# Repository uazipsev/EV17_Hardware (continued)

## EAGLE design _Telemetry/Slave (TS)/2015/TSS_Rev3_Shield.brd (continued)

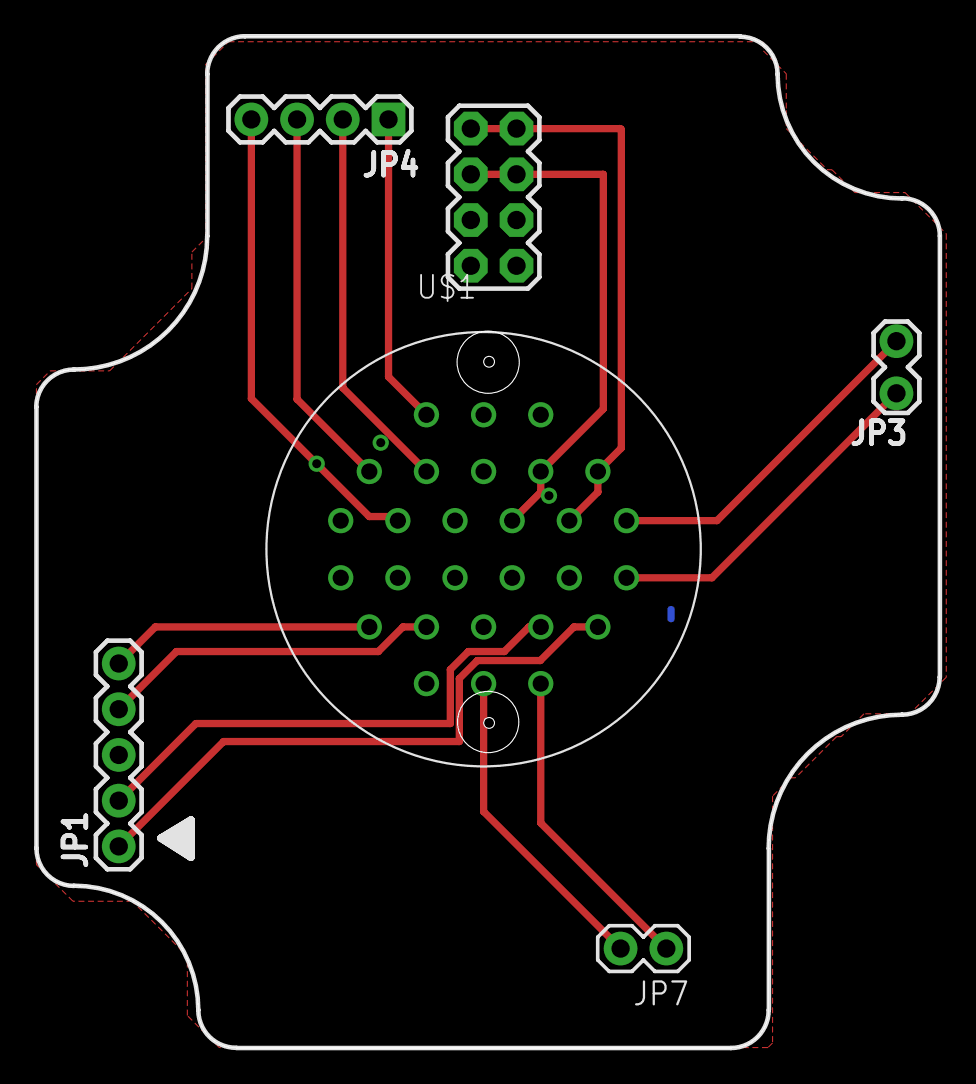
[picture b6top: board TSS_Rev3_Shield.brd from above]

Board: 2 copper layers, 50.2 x 56.2 mm, 6 parts (0 on the bottom side), 14 nets.

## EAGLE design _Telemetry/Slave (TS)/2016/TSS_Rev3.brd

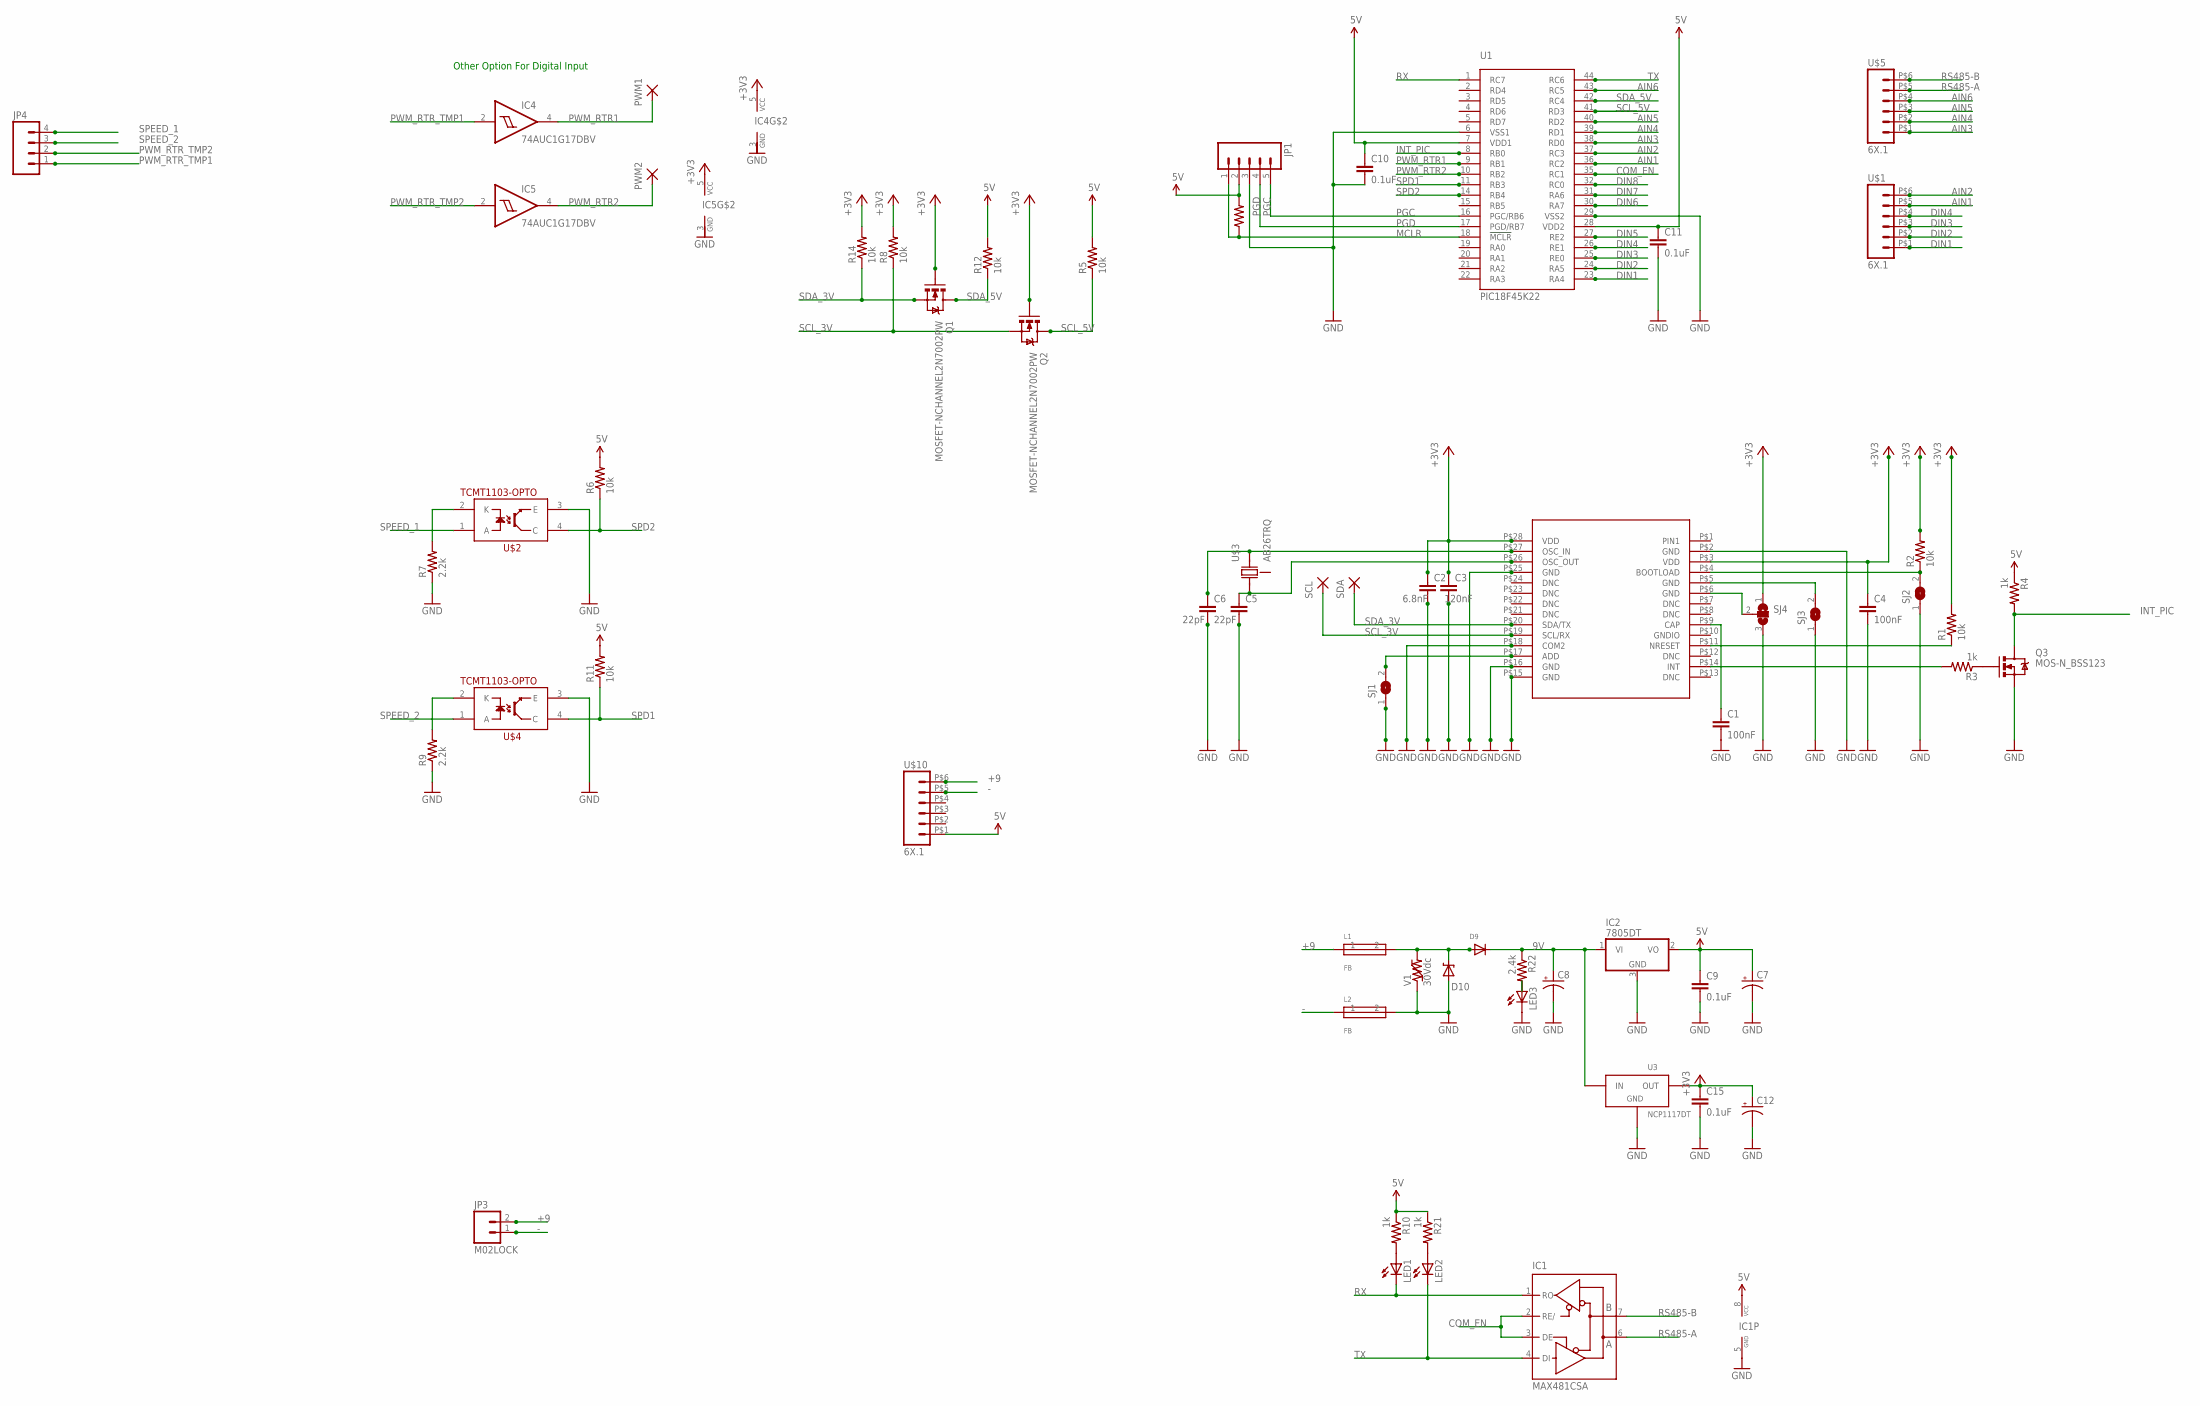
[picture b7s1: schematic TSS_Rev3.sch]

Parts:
C1, C4: 100nF; 0805
C2: 6.8nF; 0805
C3: 120nF; 0805
C5, C6: 22pF; 0805
C7, C12: CPOL-USCT3528; CT3528
C8: CAP_POL7343; EIA7343
C9, C10, C11, C15: 0.1uF; 0805
D9: DIODESOD-123; SOD-123
D10: MM5Z30; SOD-523F
IC1: MAX481CSA; SO08
IC2: 7805DT; TO252
IC4, IC5: 74AUC1G17DBV; SOT23-5
JP1: M05LOCK; 1X05_LOCK
JP3: M02LOCK; 1X02_LOCK
JP4: M04LOCK; 1X04_LOCK
L1, L2: FB; 0603
LED1, LED2, LED3: LEDCHIP-LED0805; CHIP-LED0805
PWM1, PWM2: TPSMD; 0603
Q1, Q2: MOSFET-NCHANNEL2N7002PW; SOT323
Q3: MOS-N_BSS123; SOT23
R1, R2, R5, R6, R8, R11, R12, R13, R14: 10k; 0805
R3, R4, R10, R21: 1k; 0805
R7, R9: 2.2k; 0805
R22: 2.4k; 0805
SCL: TPSMD; 0603
SDA: TPSMD; 0603
SJ1, SJ2, SJ3: SJ
SJ4: SJ2W; SJ_2
U1: PIC18F45K22; TQFP-44
U2: BOSCH_IMUSURFACEMOUNT; LGA_28
U3: NCP1117DT; DPAK
U$1, U$5, U$10: 6X.1; 1X06
U$2, U$4: TCMT1103-OPTO; SSOP-4
U$3: AB26TRQ; 3PAD_CAN
V1: 30Vdc; 0603

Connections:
5V: C7.+, C9.1, C10.1, C11.1, IC1.8 (VCC), IC2.2 (VO), JP1.2, R4.1, R5.2, R6.2, R10.1, R11.2, R12.2, R13.2, R21.1, U1.7 (VDD1), U1.28 (VDD2), U$10.P$1 (1)
9V: C8.A (+), D9.C, IC2.1 (VI), R22.1, U3.3 (IN)
+3V3: C2.1, C3.1, C4.1, C12.+, C15.1, IC4.5 (VCC), IC5.5 (VCC), Q1.1 (G), Q2.1 (G), R1.2, R2.2, R8.2, R14.2, SJ4.1, U2.P$3 (VDD), U2.P$28 (VDD), U3.2 (OUT)
+9: JP3.2, L1.1, U$10.P$6 (6)
-: JP3.1, L2.1, U$10.P$5 (5)
AIN1: U1.36 (RC2), U$1.P$5 (5)
AIN2: U1.37 (RC3), U$1.P$6 (6)
AIN3: U1.38 (RD0), U$5.P$1 (1)
AIN4: U1.39 (RD1), U$5.P$2 (2)
AIN5: U1.40 (RD2), U$5.P$3 (3)
AIN6: U1.43 (RC5), U$5.P$4 (4)
COM_EN: IC1.2 (RE/), IC1.3 (DE), U1.35 (RC1)
DIN1: U1.23 (RA4), U$1.P$1 (1)
DIN2: U1.24 (RA5), U$1.P$2 (2)
DIN3: U1.25 (RE0), U$1.P$3 (3)
DIN4: U1.26 (RE1), U$1.P$4 (4)
DIN5: U1.27 (RE2)
DIN6: U1.30 (RA7)
DIN7: U1.31 (RA6)
DIN8: U1.32 (RC0)
GHT: D9.A, D10.C, L1.2, V1.2
GND: C1.2, C2.2, C3.2, C4.2, C5.2, C6.2, C7.-, C8.C (-), C9.2, C10.2, C11.2, C12.-, C15.2, D10.A, IC1.5 (GND), IC2.3 (GND), IC4.3 (GND), IC5.3 (GND), JP1.3, L2.2, LED3.C, Q3.2 (S), R7.1, R9.1, SJ1.1, SJ2.1, SJ3.1, SJ4.3, U1.6 (VSS1), U1.29 (VSS2), U2.P$2 (GND), U2.P$15 (GND), U2.P$16 (GND), U2.P$18 (COM2), U2.P$25 (GND), U3.1 (GND), U$2.3 (E), U$4.3 (E), V1.1
INT_PIC: Q3.3 (D), R4.2, U1.8 (RB0)
MCLR: JP1.1, R13.1, U1.18 (!MCLR)
unnamed: SJ3.2, U2.P$5 (GND)
unnamed: R2.1, SJ2.2, U2.P$4 (BOOTLOAD)
unnamed: SJ4.2, U2.P$6 (GND)
unnamed: LED3.A, R22.2
unnamed: LED1.A, R10.2
unnamed: LED2.A, R21.2
unnamed: C6.1, U2.P$27 (OSC_IN), U$3.2 (OUT)
unnamed: C5.1, U2.P$26 (OSC_OUT), U$3.1 (IN)
unnamed: R7.2, U$2.2 (K)
unnamed: SJ1.2, U2.P$17 (ADD)
unnamed: R9.2, U$4.2 (K)
unnamed: R3.2, U2.P$14 (INT)
unnamed: C1.1, U2.P$9 (CAP)
unnamed: R1.1, U2.P$11 (NRESET)
unnamed: Q3.1 (G), R3.1
PGC: JP1.5, U1.16 (PGC/RB6)
PGD: JP1.4, U1.17 (PGD/RB7)
PWM_RTR1: IC4.4 (O), PWM1.1, PWM1.2, U1.9 (RB1)
PWM_RTR2: IC5.4 (O), PWM2.1, PWM2.2, U1.10 (RB2)
PWM_RTR_TMP1: IC4.2 (I), JP4.1
PWM_RTR_TMP2: IC5.2 (I), JP4.2
RS485-A: IC1.6 (A), U$5.P$5 (5)
RS485-B: IC1.7 (B), U$5.P$6 (6)
RX: IC1.1 (RO), LED1.C, U1.1 (RC7)
SCL_3V: Q2.2 (S), R8.1, SCL.1, SCL.2, U2.P$19 (SCL/RX)
SCL_5V: Q2.3 (D), R5.1, U1.41 (RD3)
SDA_3V: Q1.2 (S), R14.1, SDA.1, SDA.2, U2.P$20 (SDA/TX)
SDA_5V: Q1.3 (D), R12.1, U1.42 (RC4)
SPD1: R11.1, U1.11 (RB3), U$4.4 (C)
SPD2: R6.1, U1.14 (RB4), U$2.4 (C)
SPEED_1: JP4.4, U$2.1 (A)
SPEED_2: JP4.3, U$4.1 (A)
TX: IC1.4 (DI), LED2.C, U1.44 (RC6)

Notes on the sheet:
Other Option For Digital Input

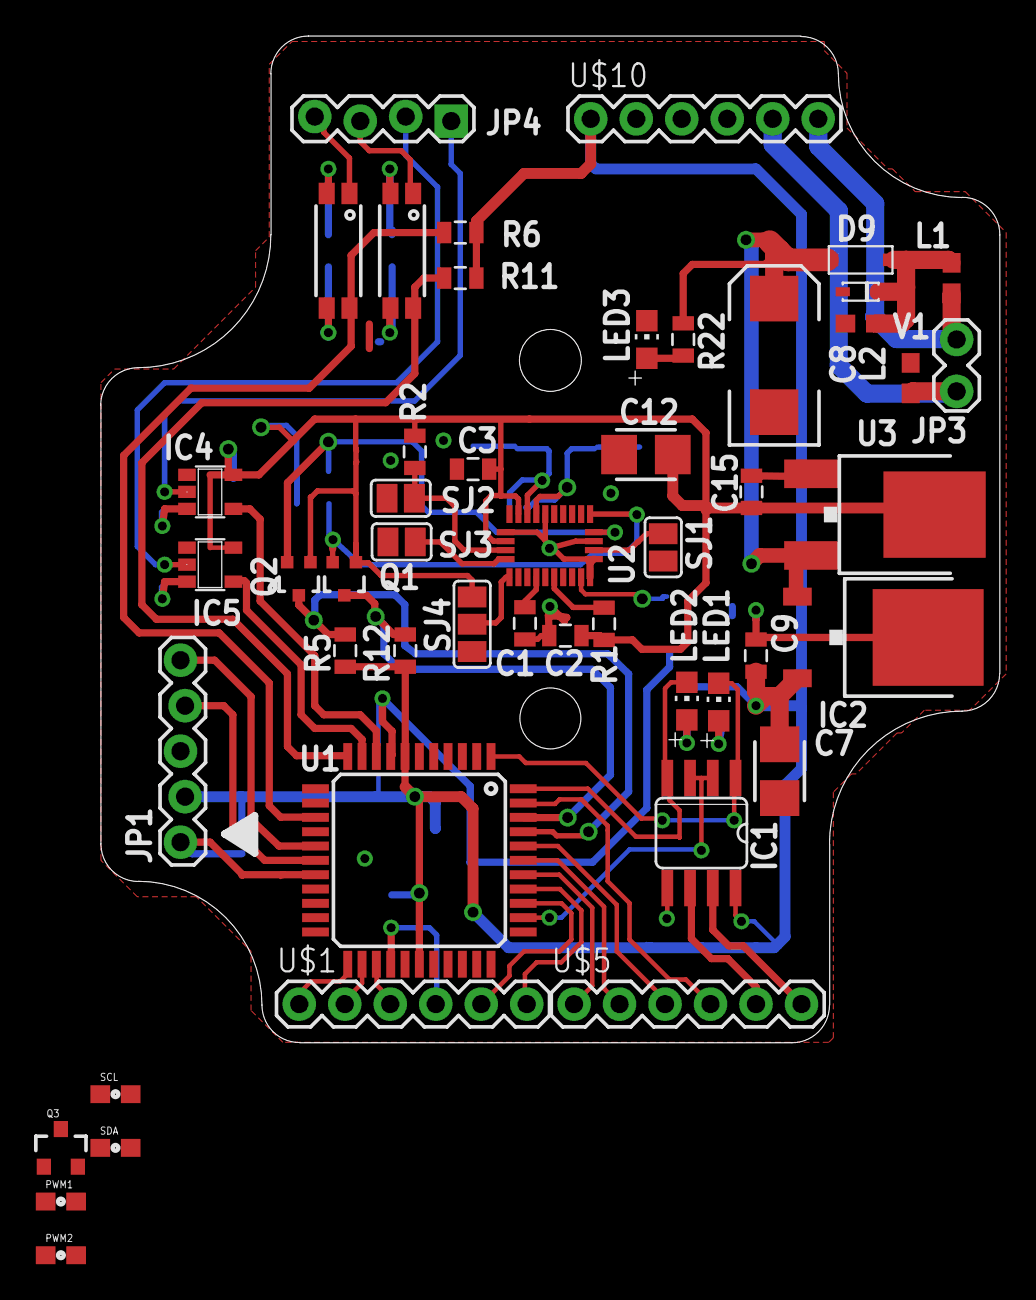
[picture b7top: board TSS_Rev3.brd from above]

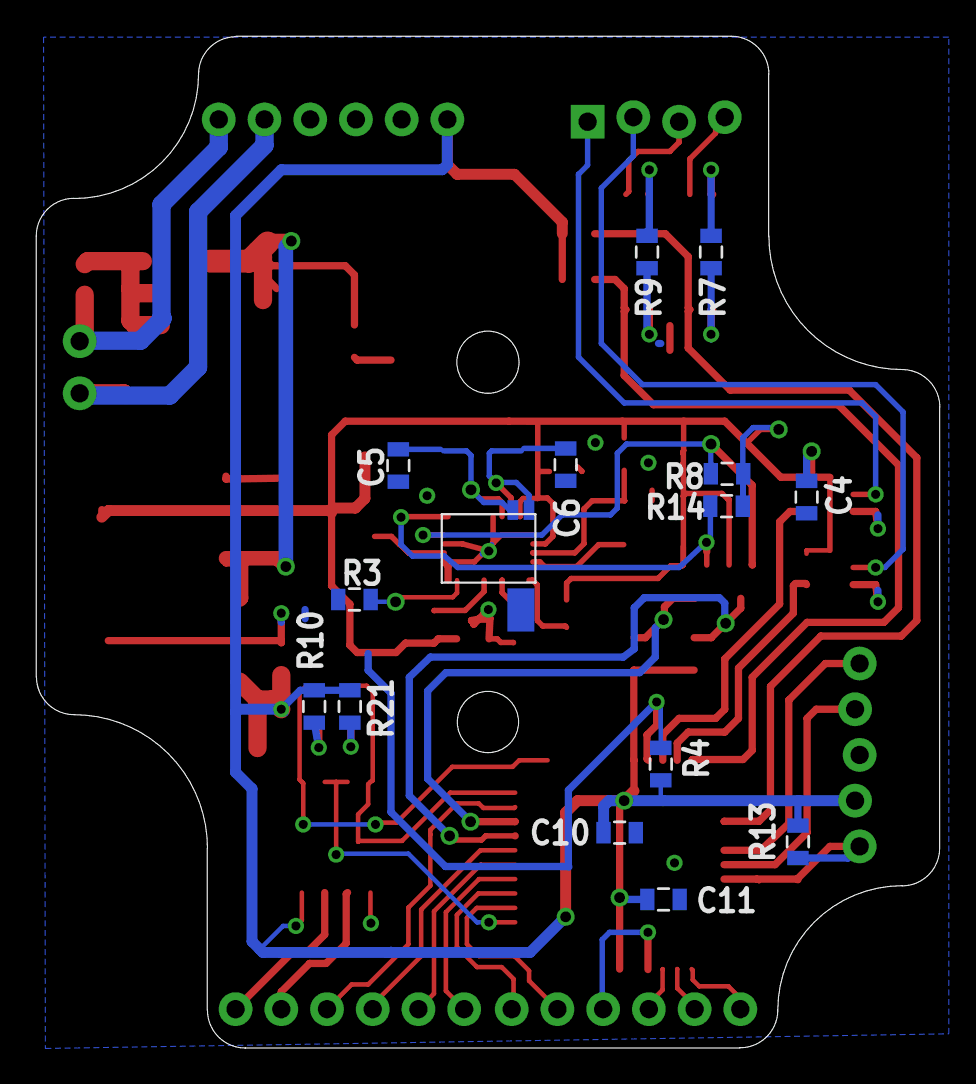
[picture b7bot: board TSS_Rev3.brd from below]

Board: 2 copper layers, 50.2 x 56.2 mm, 64 parts (15 on the bottom side), 53 nets.

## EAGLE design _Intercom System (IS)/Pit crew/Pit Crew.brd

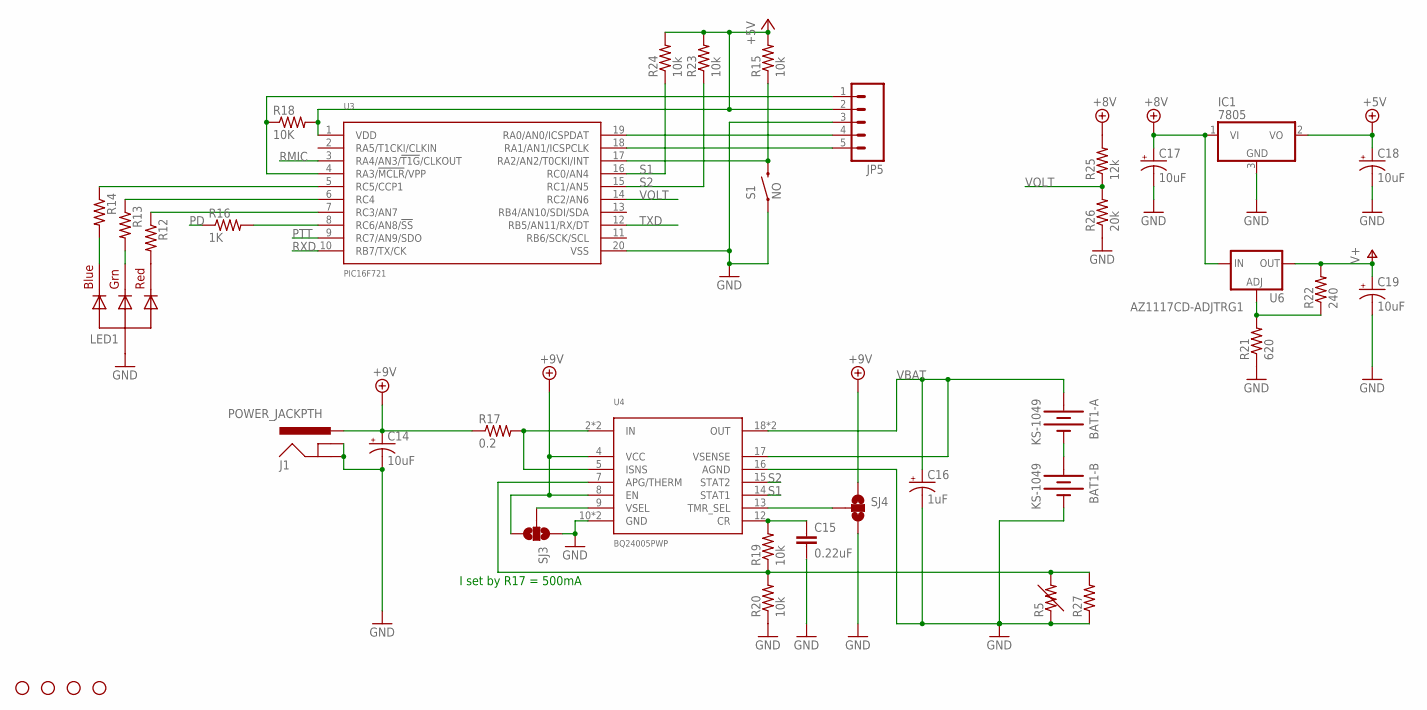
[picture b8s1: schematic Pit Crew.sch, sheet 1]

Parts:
BAT1: KS-1049; KEYSTONE_1049
C14, C17, C18, C19: 10uF; EIA3216
C15: 0.22uF; 0805
C16: 1uF; EIA3216
IC1: 7805; TO252
J1: POWER_JACKPTH; POWER_JACK_PTH
JP5: M05LOCK_LONGPADS; 1X05_LOCK_LONGPADS
LED1: RGBLED_CA-5MM; LED5MMRGB
R5, R12, R13, R14: RESISTOR0805-RES; 0805
R15, R19, R20, R23, R24: 10k; 0805
R16: 1K; 0805
R17: 0.2; R2512
R18: 10K; 0805
R21: 620; 0805
R22: 240; 0805
R25: 12k; 0805
R26: 20k; 0805
R27: R-US_0207/7; 0207/7
S1: NO; TACTILE-PTH-SIDEEZ
SJ3, SJ4: SOLDERJUMPER_2WAYS; SJ_3
STANDOFF1, STANDOFF2, STANDOFF3, STANDOFF4: STAND-OFF
U3: PIC16F721; SSOP-20
U4: BQ24005PWP; HTSSOP-20
U6: AZ1117CD-ADJTRG1; V-REG_DPACK

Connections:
+5V: C18.A (+), IC1.2 (VO), JP5.2, R15.2, R18.2, R23.2, R24.2, U3.1 (VDD); also elsewhere on the board
+8V: C17.A (+), IC1.1 (VI), R25.2, U6.3 (IN); also elsewhere on the board
+9V: C14.A (+), J1.PWR, R17.1, SJ3.3, SJ4.1, U4.4 (VCC), U4.8 (EN)
GND: BAT1.B2- (-), C14.C (-), C15.2, C16.C (-), C17.C (-), C18.C (-), C19.C (-), IC1.3 (GND), J1.GND, J1.GNDBREAK, JP5.3, LED1.2 (VCC), R5.1, R20.1, R21.1, R26.1, R27.1, S1.1, SJ3.1, SJ4.3, U3.20 (VSS), U4.10 (GND), U4.16 (AGND), U4.EP (GND); also elsewhere on the board
unnamed: BAT1.B1- (-), BAT1.B2+ (+)
unnamed: LED1.1 (RED), R12.2
unnamed: LED1.4 (BLUE), R14.2
unnamed: LED1.3 (GREEN), R13.2
unnamed: R14.1, U3.5 (RC5/CCP1)
unnamed: R13.1, U3.6 (RC4)
unnamed: R12.1, U3.7 (RC3/AN7)
unnamed: R15.1, S1.2, U3.17 (RA2/AN2/T0CKI/INT)
unnamed: R16.2, U3.8 (RC6/AN8/!SS!)
unnamed: JP5.1, R18.1, U3.4 (RA3/!MCLR!/VPP)
unnamed: JP5.4, U3.19 (RA0/AN0/ICSPDAT)
unnamed: JP5.5, U3.18 (RA1/AN1/ICSPCLK)
unnamed: R17.2, U4.2 (IN), U4.3 (IN), U4.5 (ISNS)
unnamed: R21.2, R22.1, U6.1 (ADJ)
unnamed: SJ3.2, U4.9 (VSEL)
unnamed: R5.2, R19.1, R20.2, R27.2, U4.7 (APG/THERM)
unnamed: C15.1, R19.2, U4.12 (CR)
unnamed: SJ4.2, U4.13 (TMR_SEL)
PD: R16.1; also elsewhere on the board
PTT: U3.9 (RC7/AN9/SDO); also elsewhere on the board
RMIC: U3.3 (RA4/AN3/!T1G!/CLKOUT); also elsewhere on the board
RXD: U3.10 (RB7/TX/CK); also elsewhere on the board
S1: R24.1, U3.16 (RC0/AN4), U4.14 (STAT1)
S2: R23.1, U3.15 (RC1/AN5), U4.15 (STAT2)
TXD: U3.12 (RB5/AN11/RX/DT); also elsewhere on the board
V+: C19.A (+), R22.2, U6.4 (OUT); also elsewhere on the board
VBAT: BAT1.B1+ (+), C16.A (+), U4.17 (VSENSE), U4.18 (OUT), U4.19 (OUT); also elsewhere on the board
VOLT: R25.1, R26.2, U3.14 (RC2/AN6)

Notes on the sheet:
I set by R17 = 500mA

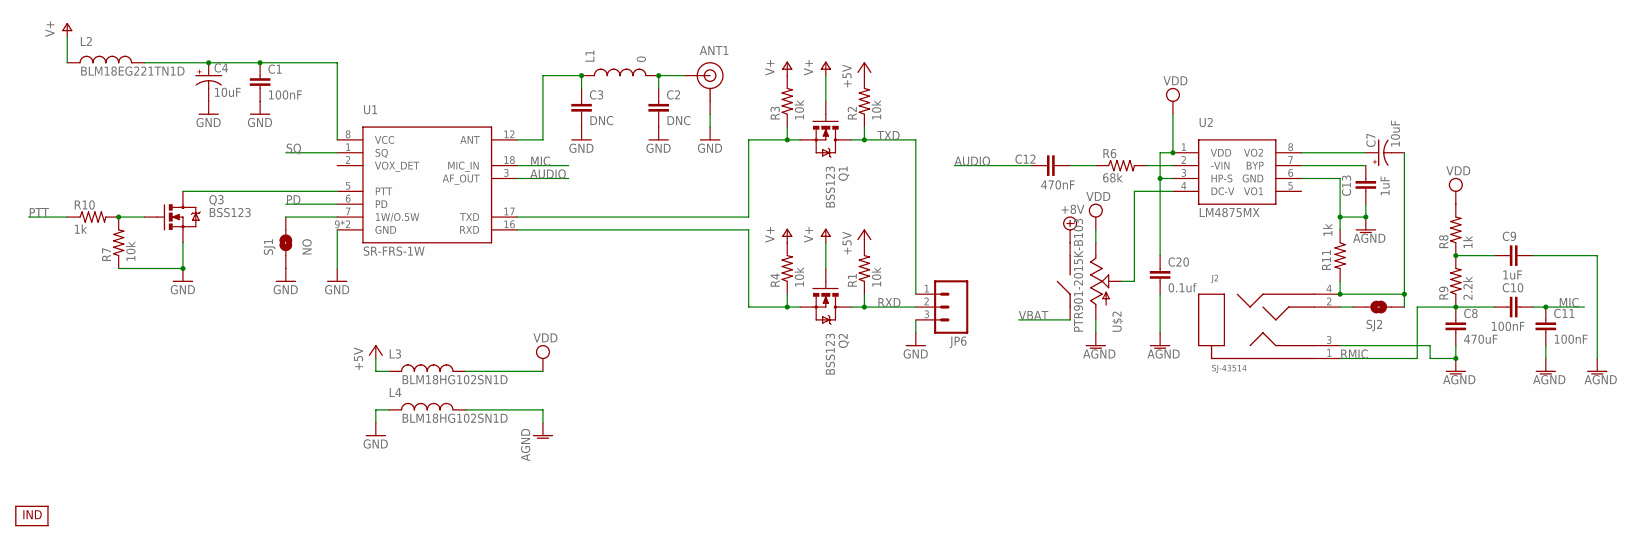
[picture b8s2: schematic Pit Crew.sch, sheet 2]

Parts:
ANT1: SMA; CONSMA002
C1, C10, C11: 100nF; 0805
C2, C3: DNC; 0805
C4, C7: 10uF; EIA3216
C8: 470uF; 0805
C9, C13: 1uF; 0805
C12: 470nF; 0805
C20: 0.1uf; 0805
J2: SJ-43514
JP6: M03LOCK; 1X03_LOCK
L1: 0; 1007
L2: BLM18EG221TN1D; 0603
L3, L4: BLM18HG102SN1D; 0603
Q1, Q2, Q3: BSS123; SOT23
R1, R2, R3, R4, R7: 10k; 0805
R6: 68k; 0805
R8, R10, R11: 1k; 0805
R9: 2.2k; 0805
SJ1: NO; SJ_2S-NO
SJ2: SOLDERJUMPERNO; SJ_2S-NO
U1: SR-FRS-1W
U2: LM4875MX; SO-8
U$2: PTR901-2015K-B103
U$3: INDPK1; PICKIT-PIN-1

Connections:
+5V: L3.1, R1.2, R2.2; also elsewhere on the board
+8V: U$2.S1; also elsewhere on the board
AGND: C8.2, C9.2, C11.2, C13.1, C20.2, J2.3, L4.2, R11.1, U2.6 (GND), U$2.1 (CCW)
AUDIO: C12.1, U1.3 (AF_OUT)
GND: ANT1.1 (GND), ANT1.2 (GND), ANT1.3 (GND), ANT1.4 (GND), C1.2, C2.2, C3.2, C4.C (-), JP6.3, L4.1, Q3.2 (S), R7.1, SJ1.1, U1.9 (GND), U1.10 (GND); also elsewhere on the board
MIC: C10.2, C11.1, U1.18 (MIC_IN)
unnamed: C3.1, L1.1, U1.12 (ANT)
unnamed: ANT1.C (SIGNAL), C2.1, L1.2
unnamed: C1.1, C4.A (+), L2.2, U1.8 (VCC)
unnamed: SJ1.2, U1.7 (1W/O.5W)
unnamed: J2.2, SJ2.1
unnamed: U2.4 (DC-V), U$2.2 (W)
unnamed: Q2.2 (S), R4.1, U1.16 (RXD)
unnamed: Q1.2 (S), R3.1, U1.17 (TXD)
unnamed: C13.2, U2.7 (BYP)
unnamed: C12.2, R6.1
unnamed: R6.2, U2.2 (-VIN)
unnamed: C9.1, R8.1, R9.2
unnamed: C7.A (+), U2.8 (VO2)
unnamed: Q3.1 (G), R7.2, R10.2
unnamed: C7.C (-), J2.4, R11.2, SJ2.2
PD: U1.6 (PD); also elsewhere on the board
PTT: R10.1; also elsewhere on the board
PTT-1: Q3.3 (D), U1.5 (PTT)
RMIC: C8.1, C10.1, J2.1, R9.1; also elsewhere on the board
RXD: JP6.2, Q2.3 (D), R1.1; also elsewhere on the board
SQ: U1.1 (SQ)
TXD: JP6.1, Q1.3 (D), R2.1; also elsewhere on the board
V+: L2.1, Q1.1 (G), Q2.1 (G), R3.2, R4.2; also elsewhere on the board
VBAT: U$2.S2; also elsewhere on the board
VDD: C20.1, L3.2, R8.2, U2.1 (VDD), U2.3 (HP-S), U$2.3 (CW)

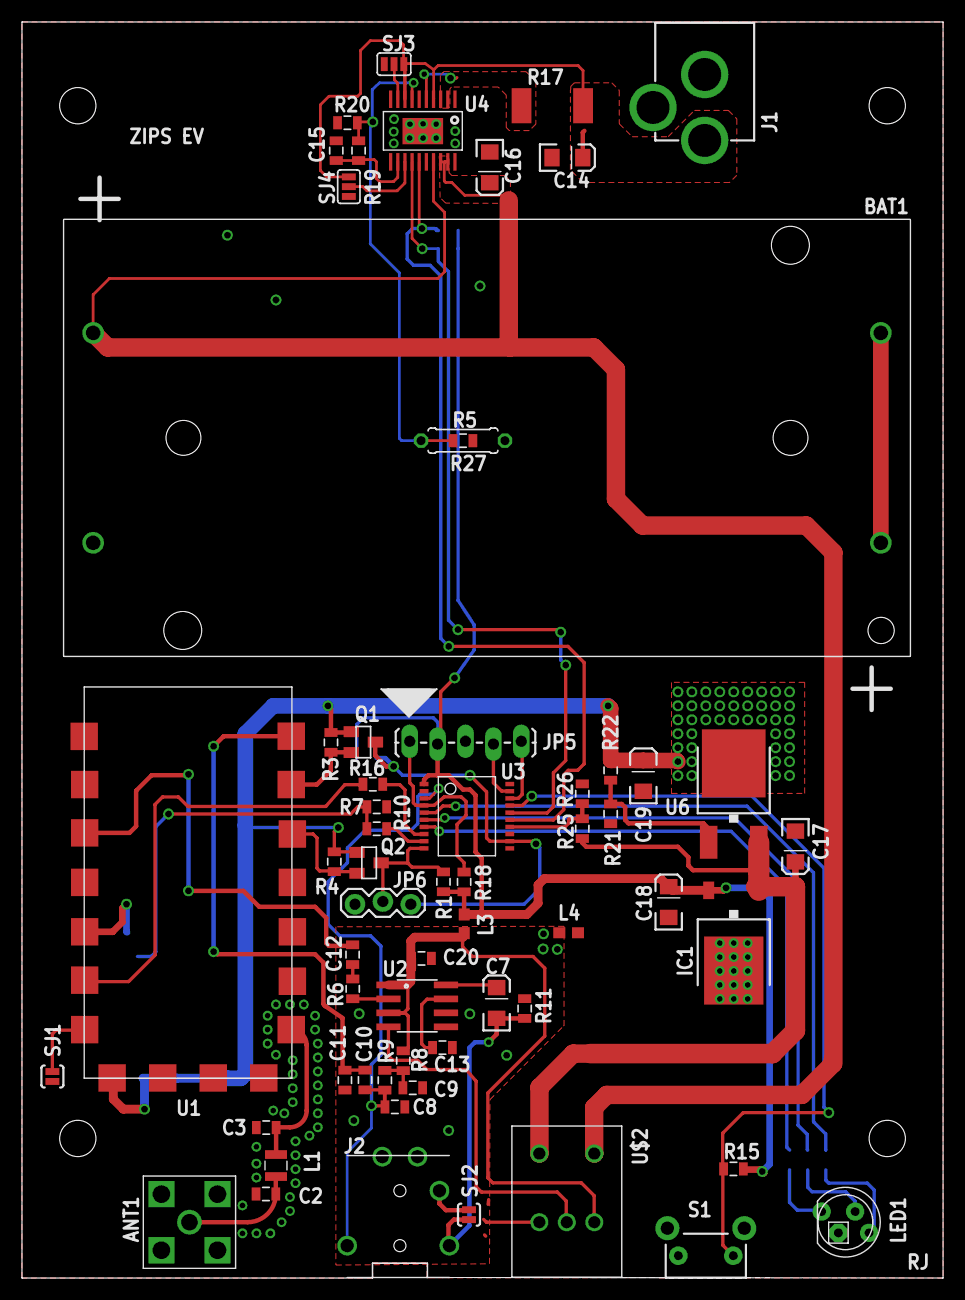
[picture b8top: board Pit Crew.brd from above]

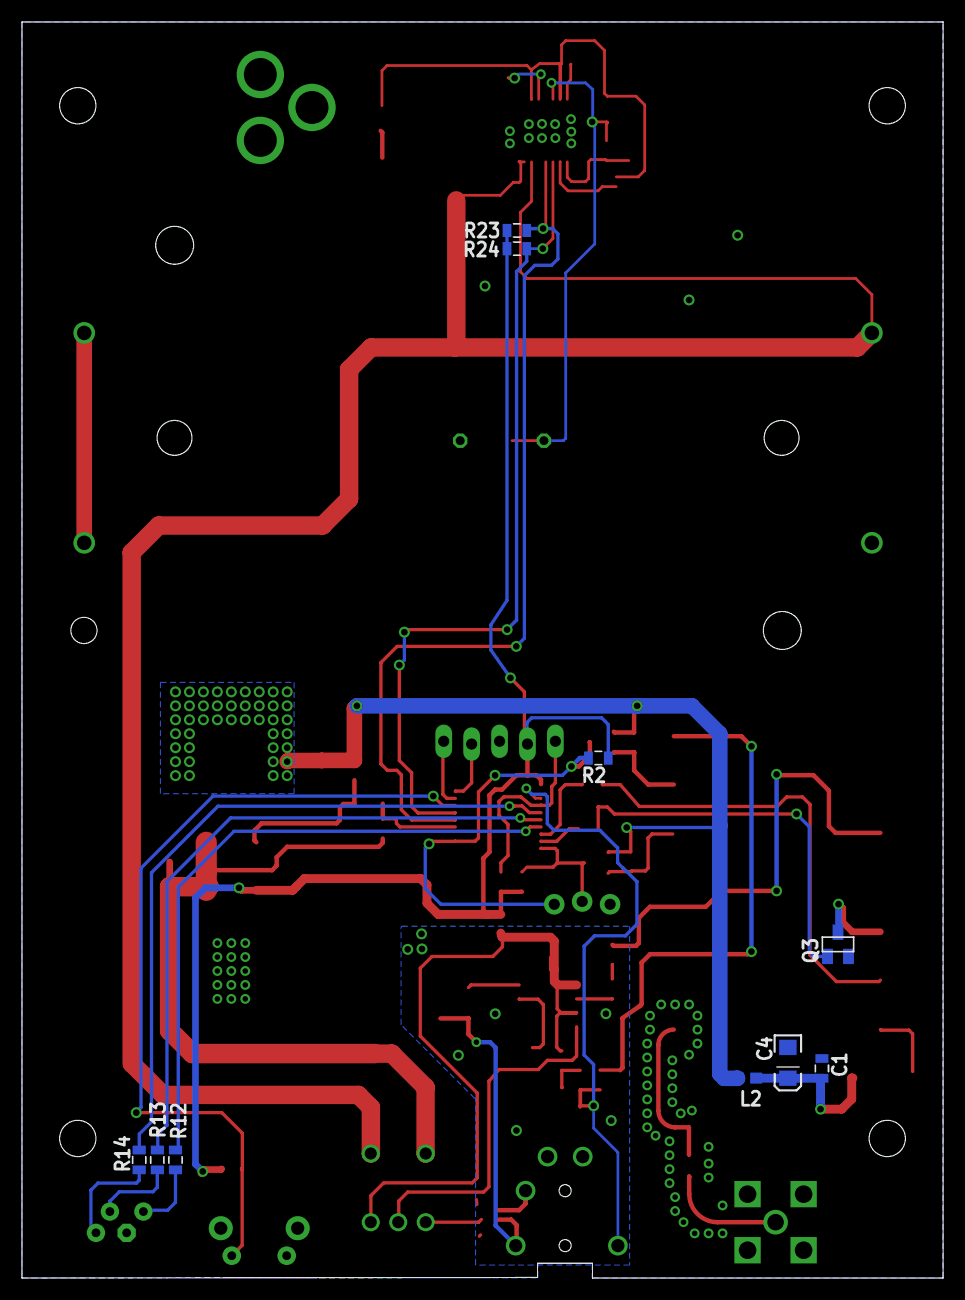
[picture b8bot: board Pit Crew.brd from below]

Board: 2 copper layers, 83.8 x 114.3 mm, 76 parts (10 on the bottom side), 52 nets.

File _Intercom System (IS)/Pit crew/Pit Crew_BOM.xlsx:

Qty-1 | Part References | Value | Package | Mfg Part Num | Mfg Name | VID | Vendor Part Num | Description | 4
6 | C5, C6, C21, C1, C10, C11 | 0.1uF | 805 | C0805C104K5RACTU | Kemet | DK | 399-1170-1-ND | CAP CER 0.1UF 50V 10% X7R 0805 | 24,399-1170-1-ND
1 | R17 | 0.2 | R2512 | RL2512FK-070R2L | Yageo | DK | 311-0.2TCT-ND | RES SMD 0.2 OHM 1% 1W 2512 | 4,311-0.2TCT-ND
1 | C15 | 0.22uF | 805 | C0805C224K5RACTU | Kemet | DK | 399-3491-1-ND | CAP CER 0.22UF 50V X7R 0805 | 4,399-3491-1-ND
7 | R8, R10, R11, R16, R12, R13, R14 | 1k | 805 | ERJ-6GEYJ102V | Panasonic Electronic Components | DK | P1.0KACT-ND | RES SMD 1K OHM 5% 1/8W 0805 | 28,P1.0KACT-ND
2 | C9, C13 | 1uF | 805 | CC0805ZRY5V7BB105 | Yageo | DK | 311-1457-1-ND | CAP CER 1UF 16V Y5V 0805 | 8,311-1457-1-ND
1 | R9 | 2.2k | 805 | ERJ-6GEYJ222V | Panasonic Electronic Components | DK | P2.2KACT-ND | RES SMD 2.2K OHM 5% 1/8W 0805 | 4,P2.2KACT-ND
5 | R1, R2, R3, R4, R7 | 10K | 805 | RC0805FR-0710KL | Yageo | DK | 311-10.0KCRCT-ND | RES SMD 10K OHM 1% 1/8W 0805 | 20,311-10.0KCRCT-ND
7 | C4, C7, C14, C16, C17, C18, C19 | 10UF | EIA3216 | F931C106MAA | AVX Corporation | DK | 478-8237-1-ND | CAP TANT 10UF 16V 20% 1206 | 28,478-8237-1-ND
5 | R15,R18, R19, R20, R23, R24 | 10k | 805 | RC0805FR-0710KL | Yageo | DK | 311-10.0KCRCT-ND | RES SMD 10K OHM 1% 1/8W 0805 | 20,311-10.0KCRCT-ND
1 | R25 | 12k | 805 | RC0805JR-0712KL | Yageo | DK | 311-12KARCT-ND | RES SMD 12K OHM 5% 1/8W 0805 | 4,311-12KARCT-ND
1 | R26 | 20k | 805 | RC0805FR-0720KL | Yageo | DK | 311-20.0KCRCT-ND | RES SMD 20K OHM 1% 1/8W 0805 | 4,311-20.0KCRCT-ND
1 | R6 | 68k | 805 | RC0805JR-0768KL | Yageo | DK | 311-68KARCT-ND | RES SMD 68K OHM 5% 1/8W 0805 | 4,311-68KARCT-ND
1 | R22 | 240 | 805 | RC0805JR-07240RL | Yageo | DK | 311-240ARCT-ND | RES SMD 240 OHM 5% 1/8W 0805 | 4,311-240ARCT-ND
2 | C8, C12 | 470nF | 805 | C0805C474K5RACTU | Kemet | DK | 399-8100-1-ND | CAP CER 0.47UF 50V X7R 0805 | 8,399-8100-1-ND
1 | R21 | 620 | 805 | RC0805JR-07620RL | Yageo | DK | 311-620ARCT-ND | RES SMD 620 OHM 5% 1/8W 0805 | 4,311-620ARCT-ND
1 | IC1 | 7805 | TO252 | MC7805BDTRKG | ON Semiconductor | DK | MC7805BDTRKGOSCT-ND | IC REG LDO 5V 1A DPAK | 4,MC7805BDTRKGOSCT-ND
1 | U$1 | AUDIO-JACK3 | AUDIO-JACK-TRRS-SMD | SJ-43514 | CUI | DK | CP-43514-ND | CONN 3.5MM AUDIO JACK 4 COND PCB | 4,CP-43514-ND
1 | U6 | AZ1117CD-ADJTRG1 | V-REG_DPACK | AZ1117CD-ADJTRG1 | Diodes Incorporated | DK | AZ1117CD-ADJTRG1DICT-ND | IC REG LDO ADJ 0.8A TO252-2 | 4,AZ1117CD-ADJTRG1DICT-ND
1 | L2 | BLM18EG221TN1D | 603 | BLM18EG221TN1D | Murata Electronics North America | DK | 490-5979-1-ND | FERRITE CHIP 220 OHM 1A 0603 | 4,490-5979-1-ND
2 | L3, L4 | BLM18HG102SN1D | 603 | BLM18HG102SN1D | Murata Electronics North America | DK | 490-1034-1-ND | FERRITE CHIP 1000 OHM 100MA 0603 | 8,490-1034-1-ND
1 | U4 | BQ24005PWP | HTSSOP-20 | BQ24005PWPR | Texas Instruments | DK | 296-25921-1-ND | IC LI-ION CHARGE MGMT 20-HTSSOP | 4,296-25921-1-ND
3 | Q1, Q2, Q3 | BSS123 | SOT23-3 | BSS123L | Fairchild Semiconductor | DK | BSS123LCT-ND | MOSFET N-CH 100V 0.17A SOT-23 | 12,BSS123LCT-ND
1 | U2 | LM4875MX | SO-8 | LM4875MX/NOPB | Texas Instruments | DK | 296-35282-1-ND | IC AMP AUDIO PWR 1W MONO 8SOIC | 4,296-35282-1-ND
1 | S1 | NO | TACTILE-PTH-SIDEEZ | EVQ-PF008K | Panasonic Electronic Components | DK | P10880S-ND | SWITCH TACTILE SPST-NO 0.02A 15V | 4,P10880S-ND
1 | U3 | PIC16F721 | SSOP-20 | PIC16F721-I/SS | Microchip Technology | DK | PIC16F721-I/SS-ND | IC MCU 8BIT 7KB FLASH 20SSOP | 4,PIC16F721-I/SS-ND
1 | J1 | POWER_JACKPTH | POWER_JACK_PTH | PJ-037A | CUI Inc. | DK | CP-037A-ND | CON PWR JCK 2.0 X 6.5MM W/O SW | 4,CP-037A-ND
1 | U$2 | PTR901-2015K-B103 | PTR901-2015K-B103 | PTR901-2015K-B103 | Bourns | DK | PTR901-2015K-B103-ND | POT 10K OHM 1/20W CARBON LINEAR | 4,PTR901-2015K-B103-ND
1 | LED1 | RGBLED_CA-5MM | LED5MMRGB | WP154A4SUREQBFZGW | Kingbright | DK | 754-1492-ND | LED RGB DIFF 5MM ROUND T/H | 4,754-1492-ND
1 | ANT1 | SMA | CONSMA002 | CONSMA002 | Linx Technologies Inc. | DK | CONSMA002-ND | CONN SMA JACK R/A 50 OHM PCB | 4,CONSMA002-ND
 |  |  |  |  |  |  |  |  | 103.38

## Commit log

2016-08-22 SS updates and fixes
2016-08-22 DDS ripup
2016-08-27 BMM cleanup
2016-08-27 Added SCH PDF
2016-08-27 File cleanup, Add pdf schematic
2016-08-27 Current sense updates
2016-09-03 Making board size change, make IO more accessible.
2016-09-04 playing w/ layout
2016-09-19 Working on BMM
2016-09-23 BMM routing
2016-10-26 Reroute
2016-12-17 Routing/ changing power supply
2016-12-17 Trying to figure out DC/DC converter
2017-01-04 added PA connector
2017-01-08 Adding traces and parts
2017-01-08 Adding parts and still routing
2017-01-08 Working on DC/DC power supply
2017-01-08 Added parts to lib
2017-03-05 Fixing layout issues.
2017-03-07 BMS Redo
2017-03-20 Found a few possible issues, made fixes.
